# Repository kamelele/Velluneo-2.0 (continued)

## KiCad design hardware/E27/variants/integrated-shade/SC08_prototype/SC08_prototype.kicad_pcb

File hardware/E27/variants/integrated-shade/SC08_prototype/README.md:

# SC08-B experimental power-board proposal

Current status (2026-11-20): the owner accepted placement at3e261d3 and the concrete one-pair input correction published at701f616 with the actual reply “zatwierdzam”. Both decisions are recorded; hardware.json now selects the approved e229 route2 spatial input. The active native PCB is fully routed:140x100mm,47parts,957segments,54vias,6filled copper zones,8managed rule areas. Native CLI refill/save DRC reports0violations/0unconnected/0parity; the independent full matrix reports PASS382861different-net face pairs. routing-verification/ contains exact saved-CAD checks. Routing-stage independent review and human acceptance are separate from this input approval; release, Gerbers for ordering, orders and energized tests remain later gates. No physical electrical or thermal qualification has been performed.

This is the owner-authorized SC08-B native working schematic, not an orderable board. Open SC08_prototype.kicad_pro; portable local libraries are included. SC07-C remains intact at commit a6c7ed424a6aa882ef7e5b46899955d3d928f09d. The actual owner selected a laboratory prototype, ambient 0..40C, with component temperatures measured on the prototype. That scope is not new-map, schematic, placement or release approval.

## Selected corrections

Remove input L1/R1. Keep the existing film capacitors in parallel (430nF); use two TE FWFU2W220RJ series input resistors. Add STTH110A (pin1cathode to U1DRAIN, pin2anode to BUS_PLUS). Replace D3 by Vishay1.5KE440A-E3/54. Replace Q2 by PMV65XP,215 (1G2S3D). Replace C4 by CL32B226KAJNNNE22uF25VX7R1210 and add parallel C10 of the same part. Change R22 to TNPW1206210KBYEA210k and R23 to RC0805FR-074K3L4.3k for the recalculated hysteresis. Six auxiliary feed resistors change from845ohm to715ohm (CRCW2512715RFKEGHP). Their localambient condition is90C maximum; U3 effective thermal resistance must not exceed85K/W. R23limits100uAhotleakage plus5uAreserve toanOFFnode below0.5V, conditional on gateOFFstate. Other SC07 functionality, both separately fed PhotoMOS paths, base150uF160V reservoir and470ohm5W reconnect resistor remain.

The approved map contains47positions112physicalpins30nets andoneNC. Review complete physical-pin-intent.csv. New part identities and footprint geometry must be checked at capture; generic library identifiers are proposals, not a claim of completed native pad verification.

## What is actually calculated

Q2 has a manufacturer hot RDSon maximum at150C, eliminating reliance on a PNP saturation assumption. Recalculation gives5.019..6.401V gate drive, at least5.345mA to each PhotoMOS under stated rail/LED/resistor bounds,1.299mA minimum shunt current, and conditional retry below25Hz. Auxiliary-feed and local80C/85K/W U3 thermal budgets are explicit, not achieved temperatures.

Removing L1 eliminates its saturation/resonance mechanism. Peak-line connection current is bounded0.903A in the scalarRC network, total resistor energy30.28mJ. The chosen positive1kV engineering test envelope is bounded by1100V3us then60us half-value tail. With Cin>=387nF and RFpair>=396.264ohm, analytical BUS<=663.947V even with TVSopen. A700V switch still needs actual SOURCE/loop/probe margins; proposed measured VDS target is680V. The2.2kV version gives970.098V and FAILS. No general2kV or IECsurge compliance is claimed.

Whole-pulse source-energy inequality p=vs*i-R*i²<=vs²/(4R) gives COUT<=141.846V for the explicit1kV envelope, starting132V (rounded above recalculated131.086V maximum trip),120uF,shutdown.6ms and imposed1.4A residual-current bound. This does not prove a current limiter or response time. Proposed experimental fault acceptance ceiling145V replaces the earlier135V criterion only if the owner approves this packet. It stays below160V capacitor rating but requires updated pulse/discharge/fault review.

The actual own RC/samplehold21-case screen with CFB18/44/52.8uF gives averageLED43.890..58.808mA, maximumCOUT113.233V, and input-resistor pair loss up to2.681W. It is a sensitivity model, not manufacturer SPICE/PIXls or a guaranteed full-temperature envelope. Exact55mA is a calibration target; initialR2=28.7ohm, with candidate unpowered substitution menu22.1..31.6ohm to be evaluated under an engineering change. The earlier trim study is explicitly historical SC07 ideal-source evidence and is not a SC08 result.

## Prototype acceptance and physical evidence

The proposed prototype criteria in prototype-validation.json name quantities, corners and stop limits. They are plans and conditions, not completed tests. No mains, thermal, surge, optical or fault measurements occurred. Currentaccuracy, single surviving actuator attemperature, Ceff and continuous/repeated-fault resistorheat remain to be verified. In particular, the energy bound protects neither R7 against indefinite overload nor a LED module against arbitrary simultaneous faults.

Local heat is a real cost: inputresistors roughly2..2.7Wpair, auxiliaryfeed about2W, R7 about1.42W at55mA, plus IC/inductor losses. No small bulb-base size, efficiency or800lm is yet demonstrated. Placement must separate heat sources, provide solder/test access and allow qualified thermal measurements. A futureLYT5 design could reduce auxiliary loss, but requires different sensing, custom bias-wound magnetics and an actual design-tool run; it is not selected as a ready replacement.

All17 original product requirements remain controlling for the finishedlamp; original-requirements-impact.json records what this experimental scope does and does not address. Neither a prototype scope nor ERC authorizes marking physical qualification complete. No broad waivers or relaxed global rules are introduced. The standard0.2mm fabrication minimum is not a mains insulation rule. Allinput/output nets are hazardous mains-referenced; prototype testfixture/accessibility/insulation and standards assessment remain separate gates.

## Next controlled step

Actual owner approval of this exact new map and the experimental145V/test-envelope proposal is recorded in owner-capture-approval.json. Native capture is completed and checked; The owner subsequently accepted commit910870c as the experimental laboratory schematic; The owner subsequently accepted the separate LAB/spatial input and actual placement at3e261d3. Routing-stage completion and acceptance are still pending. The toolkit requires independent spatial intent before PCB placement and routing/release reviews before manufacturing files. No Gerbers, purchase or energized tests are authorized by this packet.

Primary sources: Nexperia PMV65XP product data12Feb2013; Samsung CL32B226KAJNNN official product page; ST STTH110 DS3067; Vishay88301Rev09Aug2022; TE6-2176792-5; PowerIntegrations LYT0RevB/AN60. Exact URLs are retained in the BOM and research records. Research actors and evidence limits are disclosed in workflow/schematic-08 review records.

Native capture checks are retained in workflow/integrated-shade/schematic-08/capture-checks. Requirements retain all17 original obligations; imported historical evidence is isolated under reference/SC07 and is not SC08 qualification. Native placement and partial routing now exist as stated above. No physical electrical, thermal, surge or fault test has been performed. Generic fabrication rules are not mains insulation rules.

Current PCB preparation is defined by pcb-basis/DESIGN_AUTHORITY.md and the proposed LAB fabrication crosswalk. This is a bare unpowered test-board scope proposal; original17product obligations remain in requirements.json. The actual schematic-stage prototype decision is recorded under workflow/schematic-08/pcb-planning/owner-schematic-prototype-decision.json. No PCB placement, routing or purchase acceptance follows from that decision.

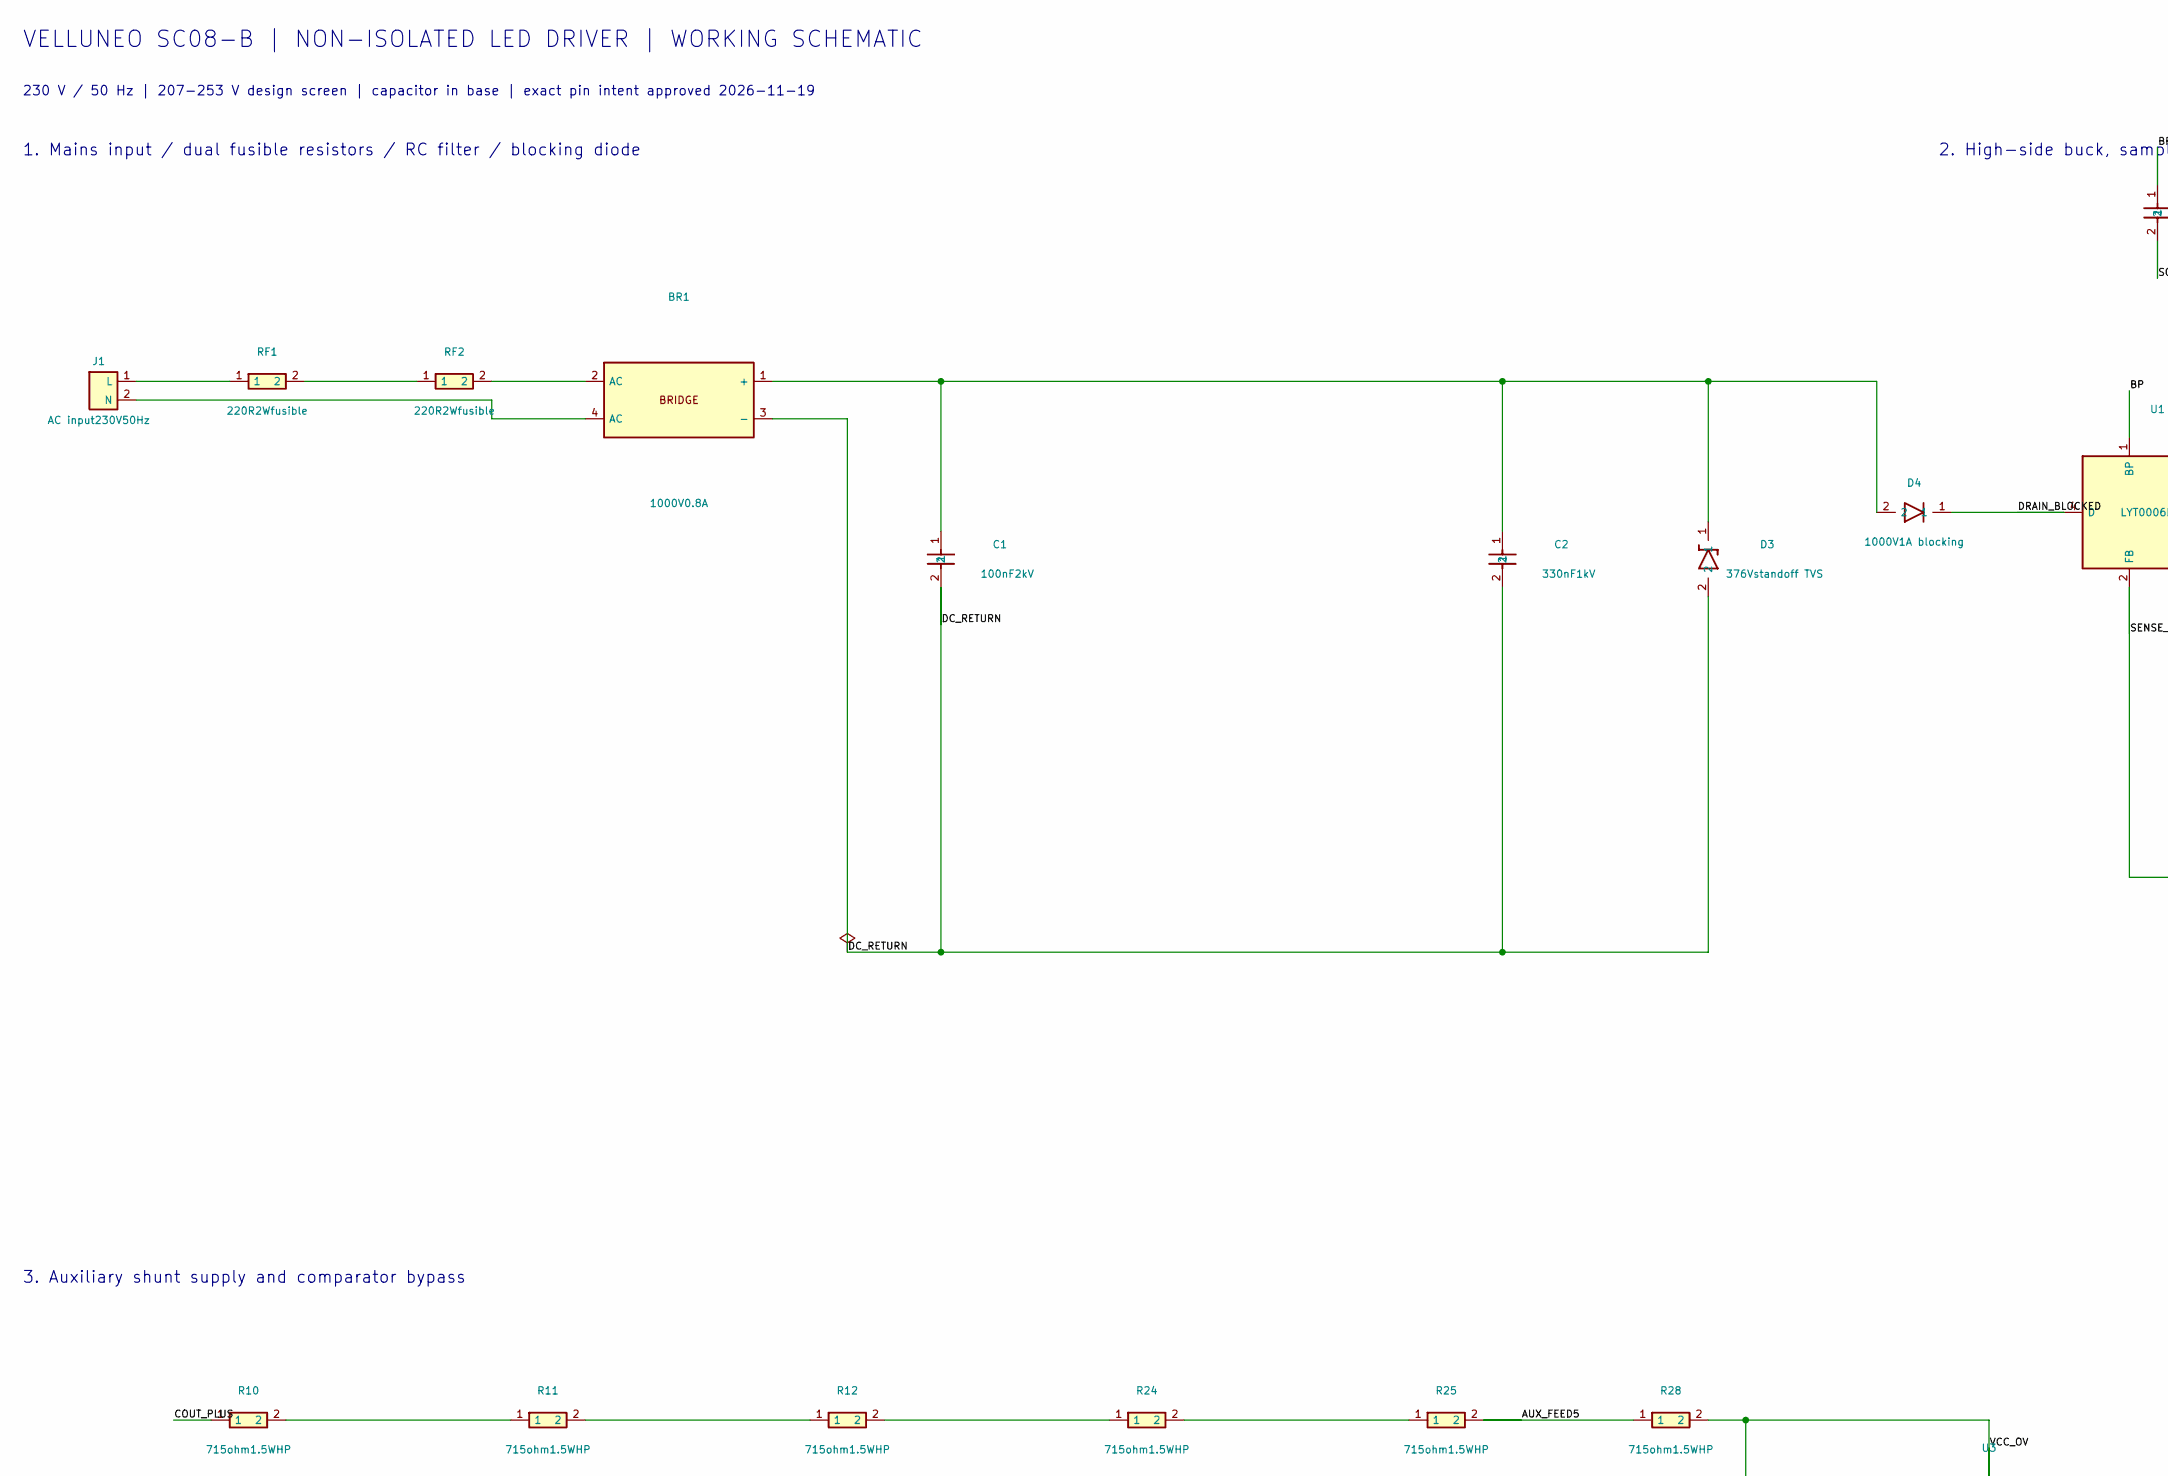
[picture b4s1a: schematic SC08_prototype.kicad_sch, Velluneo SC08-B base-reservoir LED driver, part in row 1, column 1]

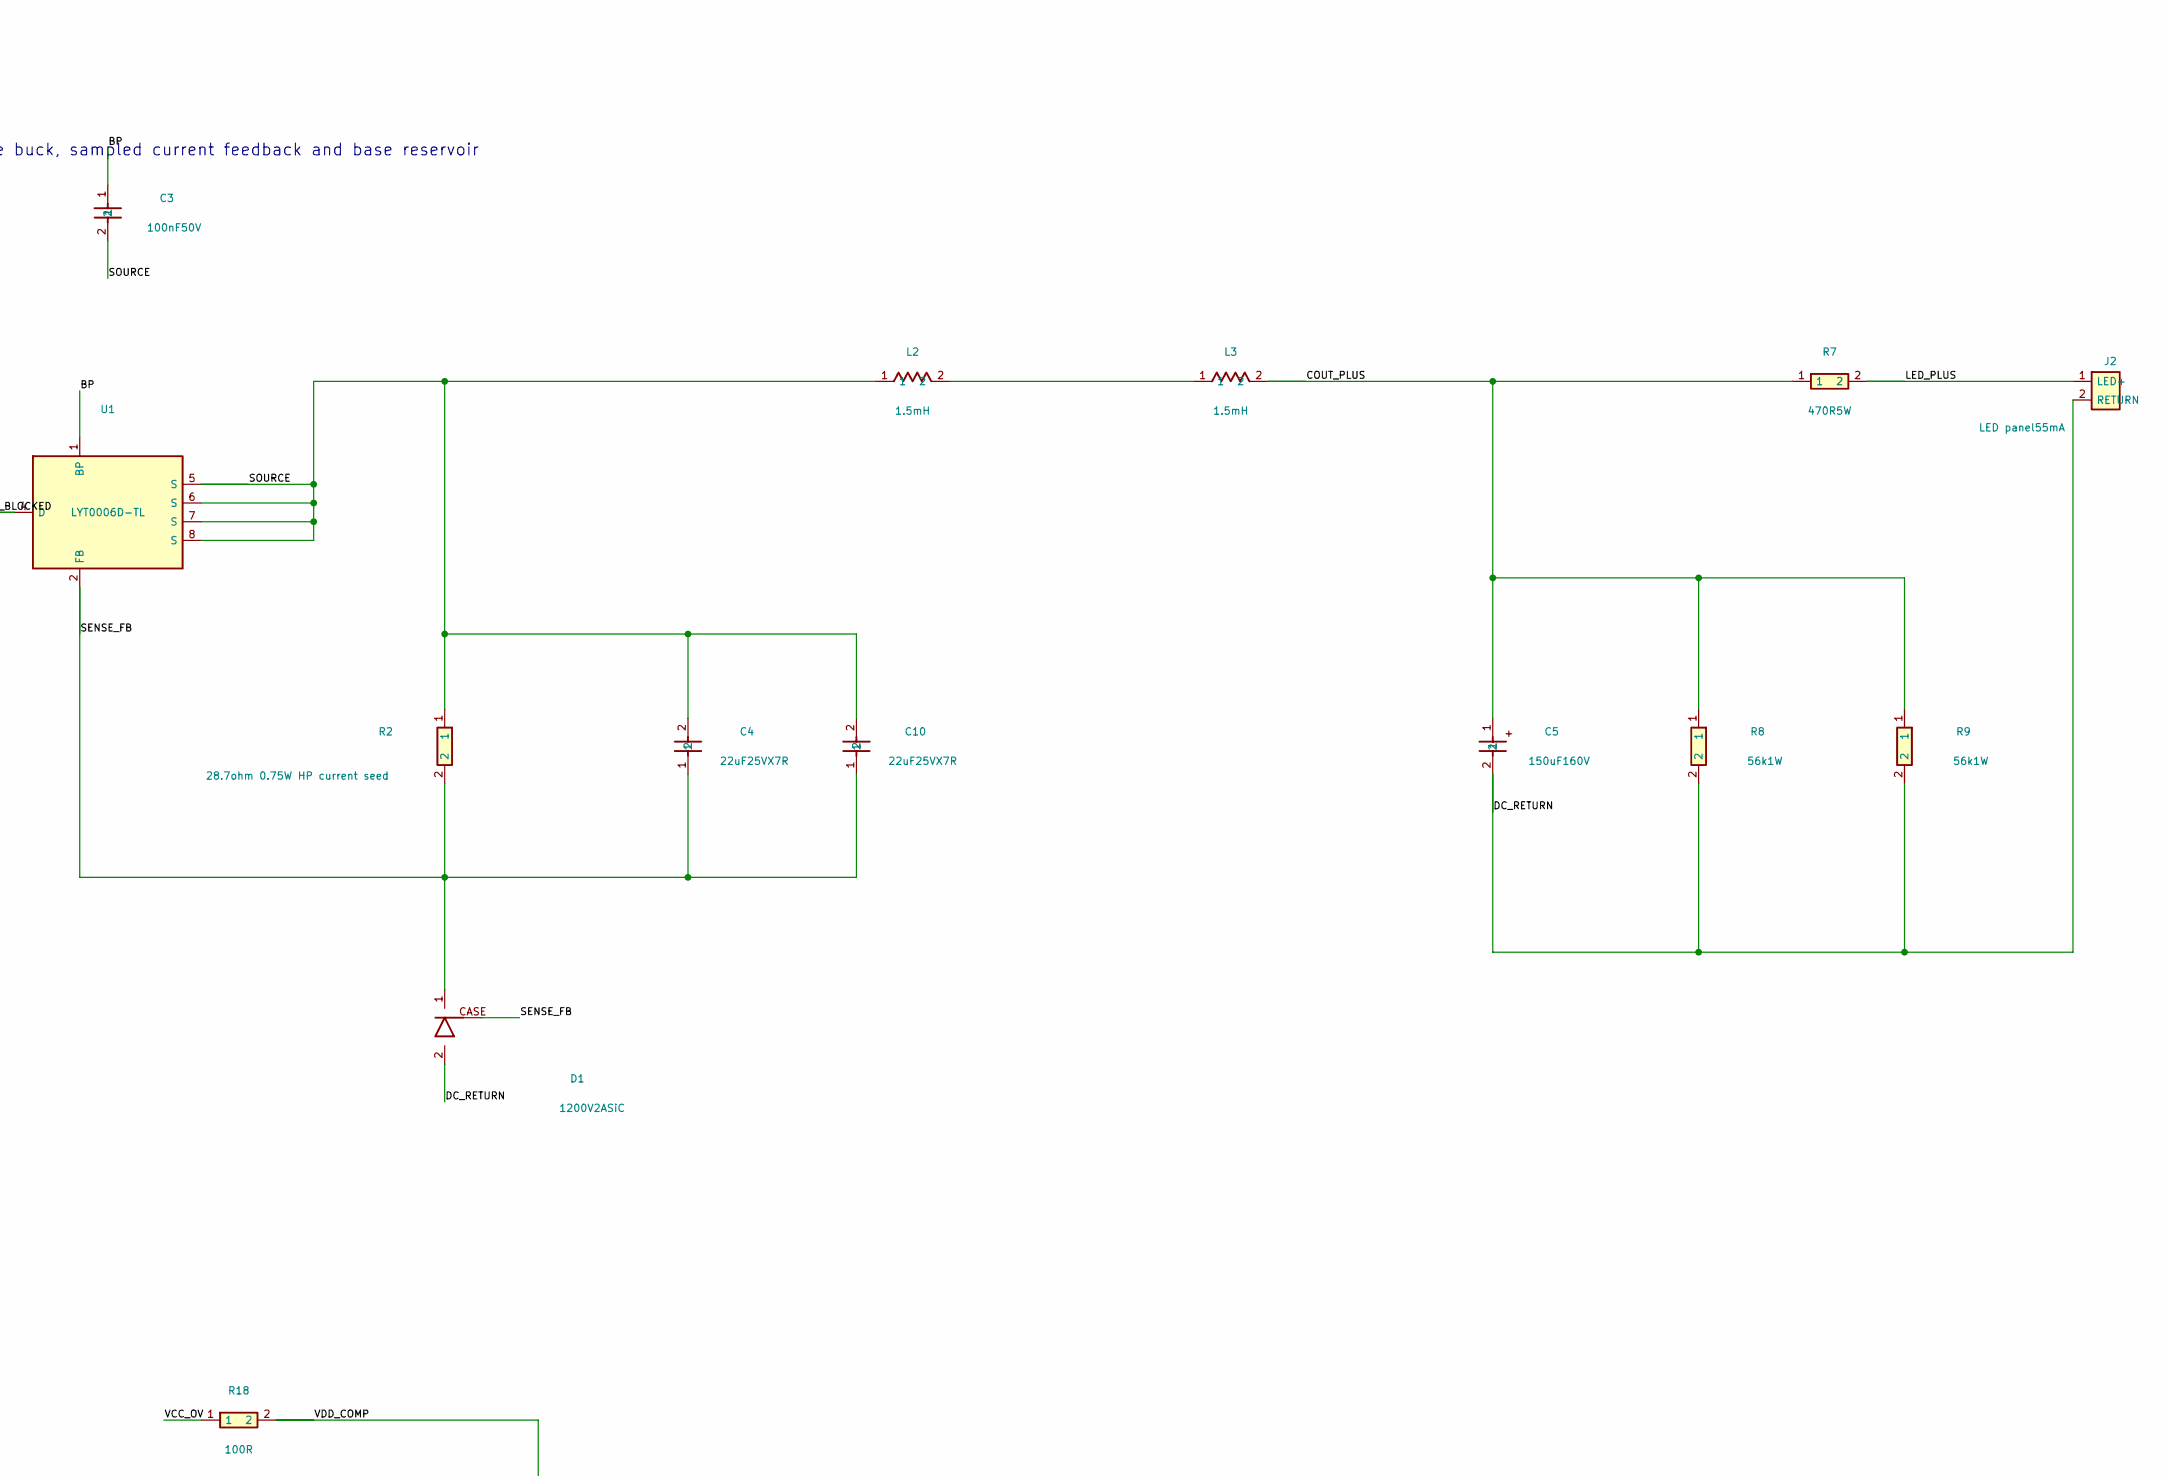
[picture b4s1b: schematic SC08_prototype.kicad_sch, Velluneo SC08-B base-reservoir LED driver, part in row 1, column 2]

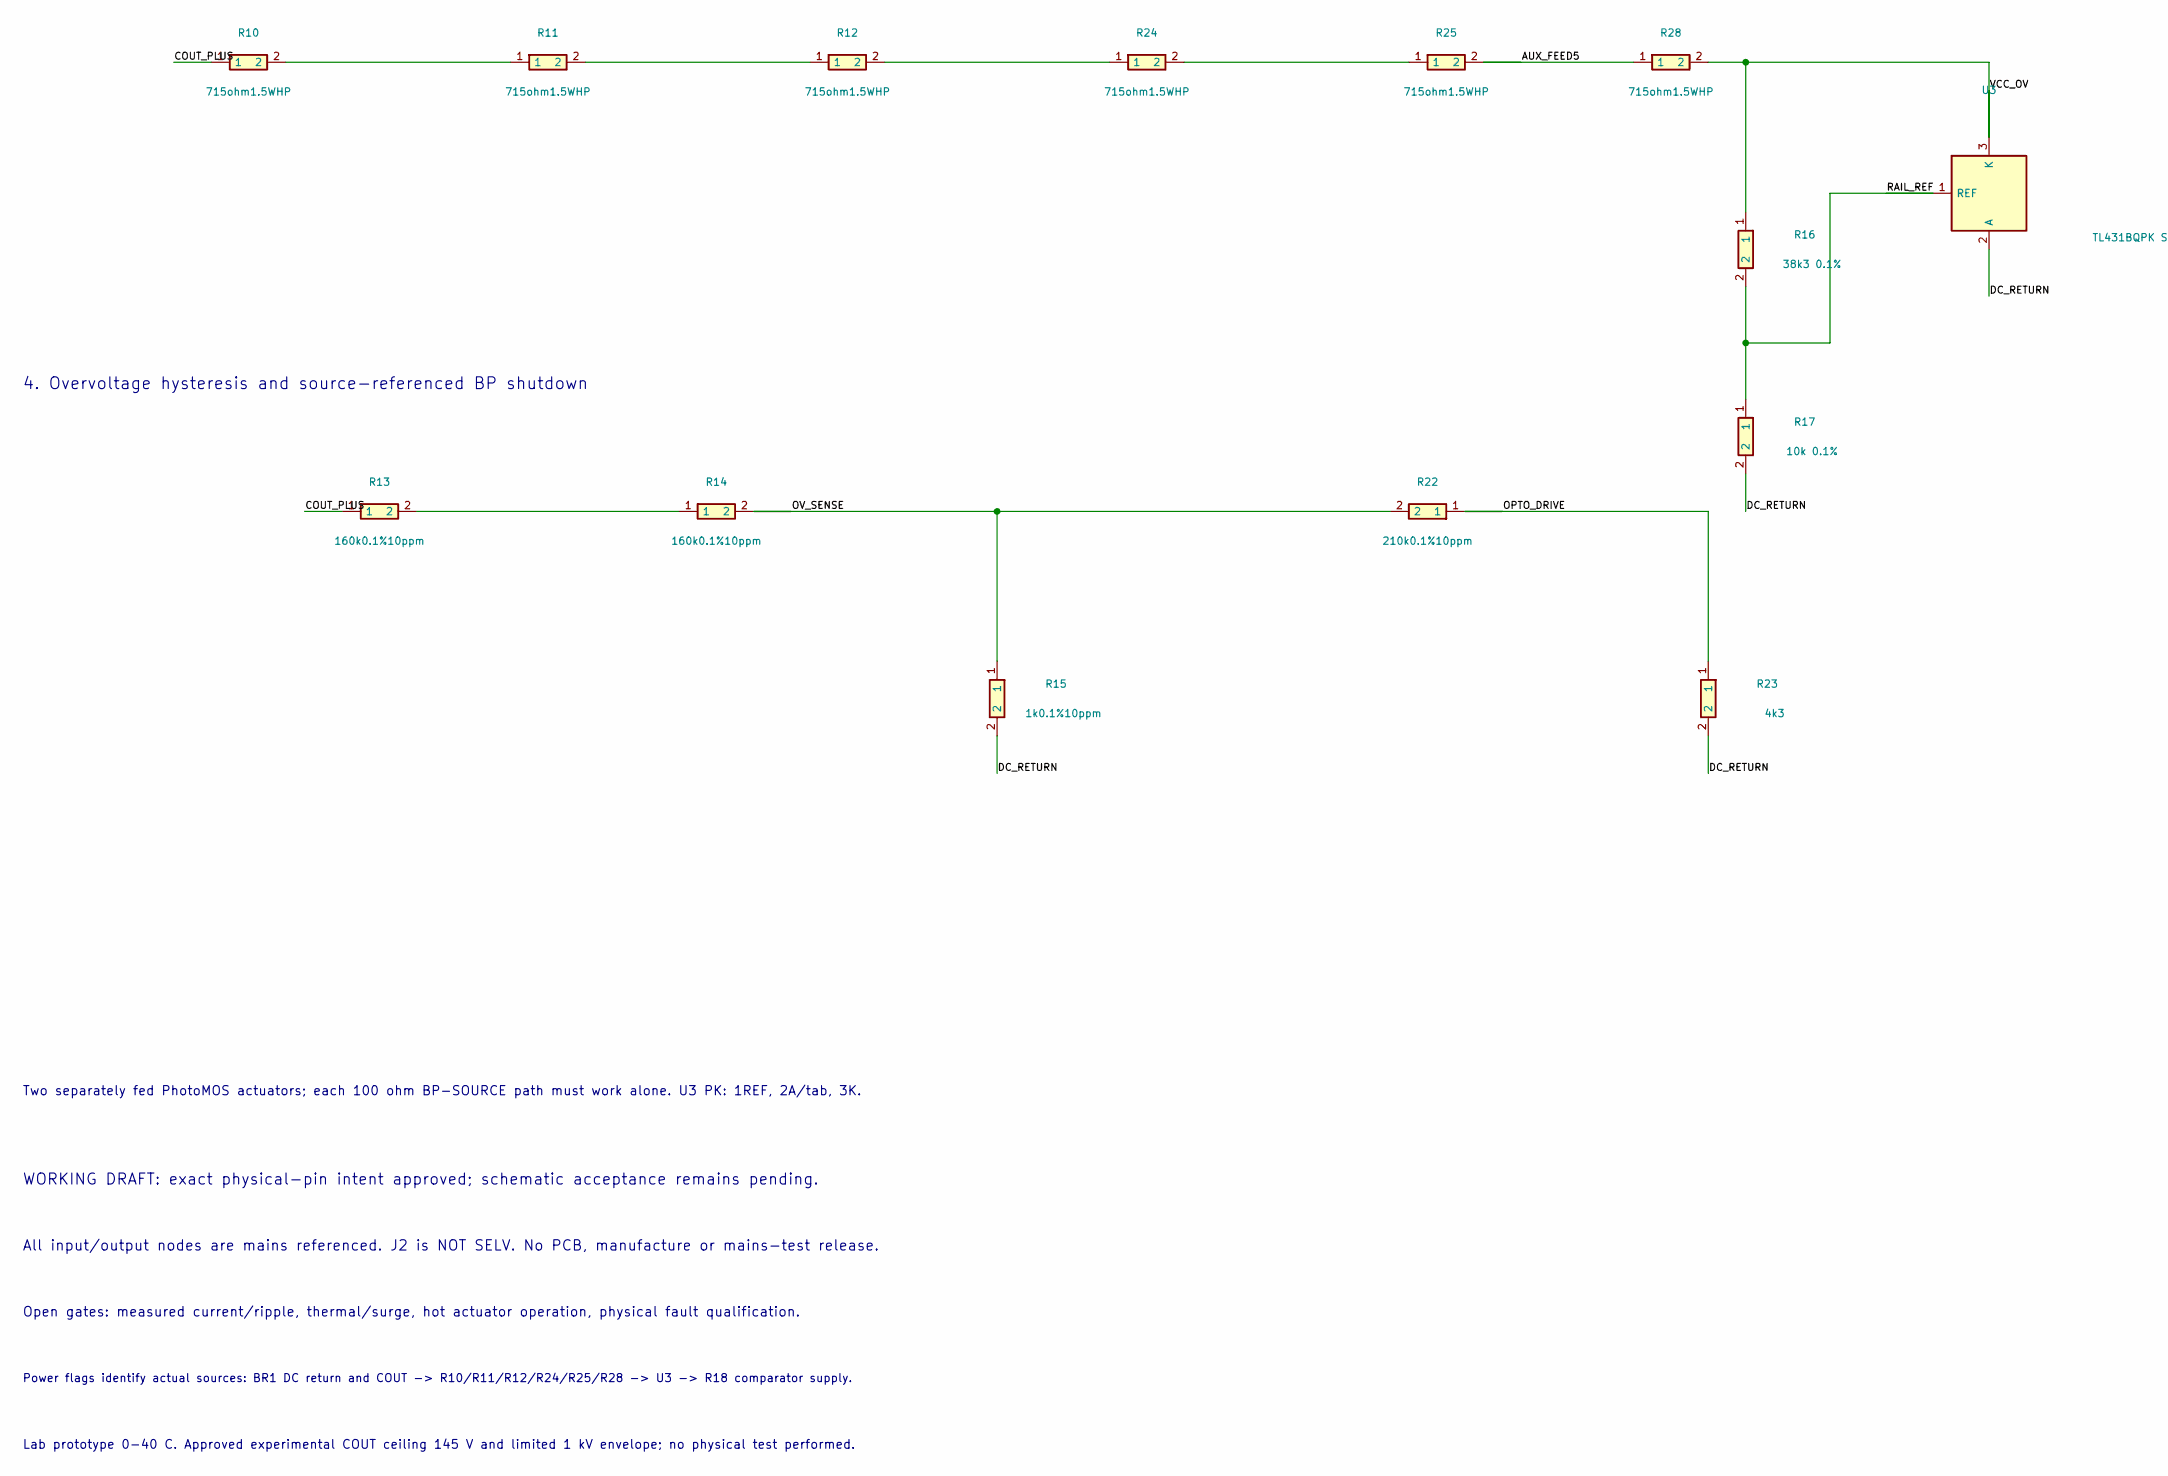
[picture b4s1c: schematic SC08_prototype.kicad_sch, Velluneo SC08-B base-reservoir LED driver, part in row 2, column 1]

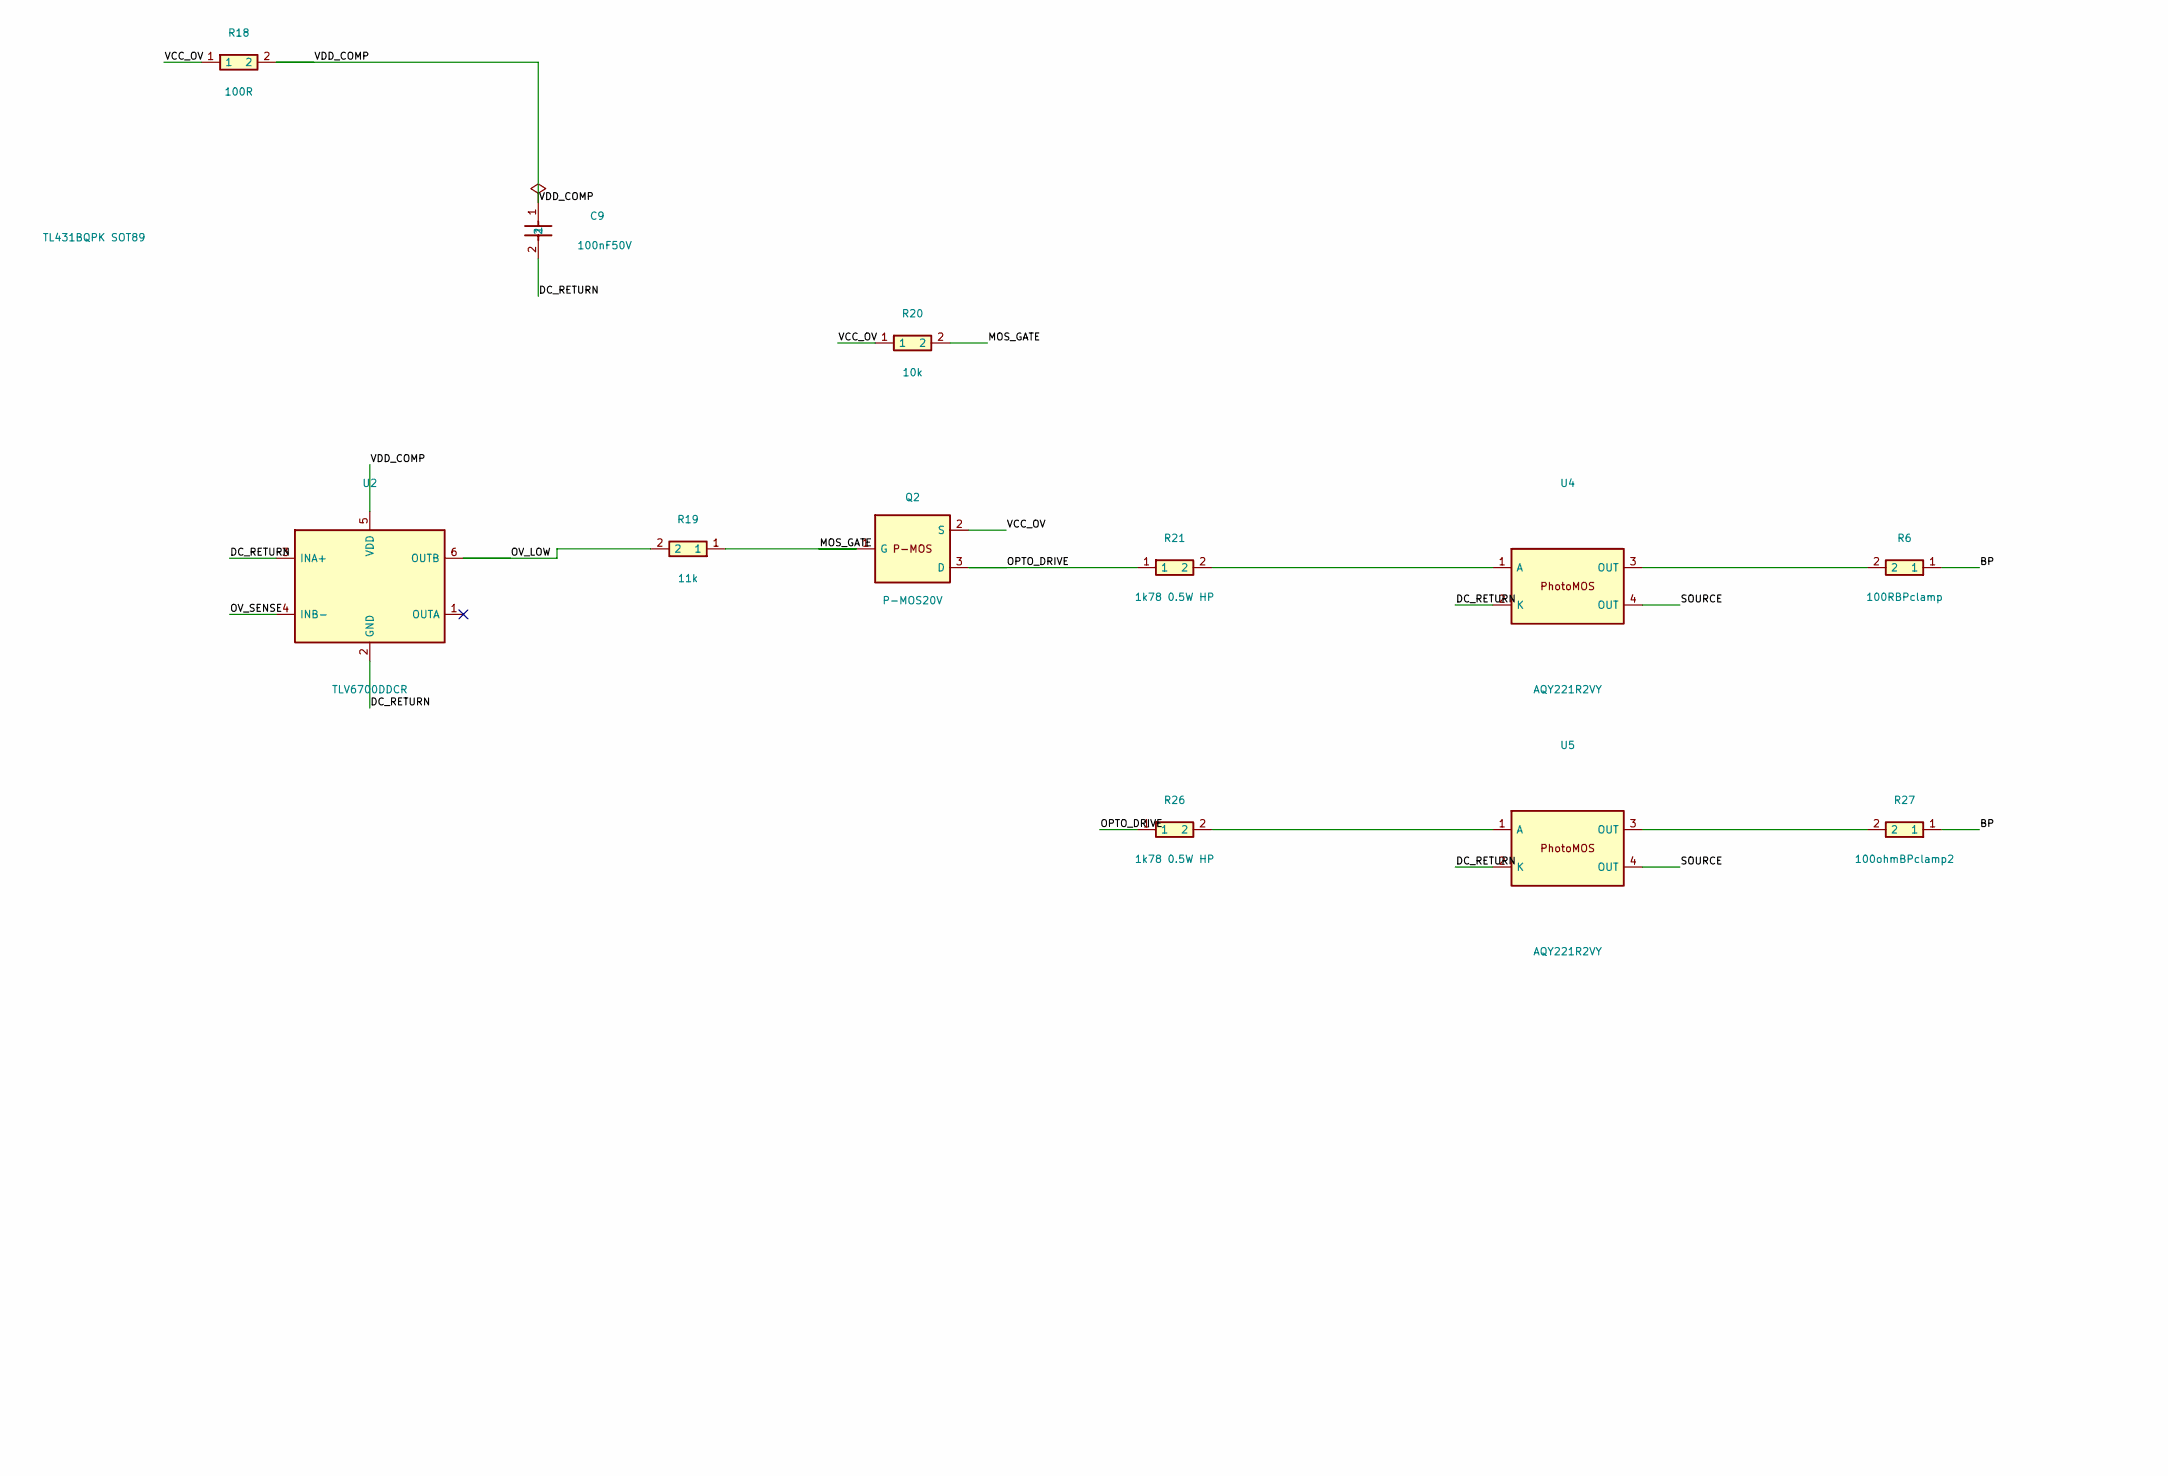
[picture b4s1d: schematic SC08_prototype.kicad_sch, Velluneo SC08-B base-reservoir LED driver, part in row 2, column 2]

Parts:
BR1: 1000V0.8A; MB10S_Diodes; MPN MB10S-13
C1: 100nF2kV; Film_32x14_P27p5; MPN R76UR31004030J
C2: 330nF1kV; Film_32x14_P27p5; MPN R76QR3330SE30J
C3, C9: 100nF50V; C_0805; MPN GRM21BR71H104KA01L
C4, C10: 22uF25VX7R; C_1210_3225Metric; MPN CL32B226KAJNNNE
C5: 150uF160V; CP_16x25_P7p5; MPN EEUED2C151
D1: 1200V2ASiC; C4D02120E_TO252; MPN C4D02120E
D3: 376Vstandoff TVS; D_DO-201AD_P15.24mm_Horizontal; MPN 1.5KE440A-E3/54
D4: 1000V1A blocking; D_SMA; MPN STTH110A
J1: AC input230V50Hz; WirePads_2_P7p5; MPN PCB wire pads, not purchased connector
J2: LED panel55mA; WirePads_2_P7p5; MPN PCB wire pads, not purchased connector
L2, L3: 1.5mH; RFC1010B_P6; MPN RFC1010B-155KE
Q2: P-MOS20V; SOT23; MPN PMV65XP,215
R2: 28.7ohm 0.75W HP current seed; R_1206; MPN CRCW120628R7FKEAHP
R6: 100RBPclamp; R_0805; MPN RC0805FR-07100RL
R7: 470R5W; AC05_18x7p5_P25p4; MPN AC05000004700JAC00
R8, R9: 56k1W; R_2512; MPN CRCW251256K0FKEG
R10, R11, R12, R24, R25, R28: 715ohm1.5WHP; R_2512; MPN CRCW2512715RFKEGHP
R13, R14: 160k0.1%10ppm; R_1206; MPN TNPW1206160KBYEA
R15: 1k0.1%10ppm; R_1206; MPN TNPW12061K00BYEA
R16: 38k3 0.1%; R_1206; MPN TNPW120638K3BEEA
R17: 10k 0.1%; R_1206; MPN TNPW120610K0BEEA
R18: 100R; R_0805; MPN RC0805FR-07100RL
R19: 11k; R_0805; MPN RC0805FR-0711KL
R20: 10k; R_0805; MPN RC0805FR-0710KL
R21, R26: 1k78 0.5W HP; R_0805; MPN CRCW08051K78FKEAHP
R22: 210k0.1%10ppm; R_1206; MPN TNPW1206210KBYEA
R23: 4k3; R_0805; MPN RC0805FR-074K3L
R27: 100ohmBPclamp2; R_0805; MPN RC0805FR-07100RL
RF1, RF2: 220R2Wfusible; RF_16x5p5_P22; MPN FWFU2W220RJ
U1: LYT0006D-TL; LYT_SO8C_no3; MPN LYT0006D-TL
U2: TLV6700DDCR; SOT23_6; MPN TLV6700DDCR
U3: TL431BQPK SOT89; SOT-89-3; MPN TL431BQPK
U4, U5: AQY221R2VY; Panasonic_SSOP4; MPN AQY221R2VY

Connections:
/AUX_FEED5: R25.2, R28.1
/BP: C3.1, R6.1, R27.1, U1.1 (BP)
/COUT_PLUS: C5.1, L3.2, R7.1, R8.1, R9.1, R10.1, R13.1
/DC_RETURN: BR1.3 (-), C1.2, C2.2, C5.2, C9.2, D1.2 (A), D3.2, J2.2 (RETURN), R8.2, R9.2, R15.2, R17.2, R23.2, U2.2 (GND), U2.3 (INA+), U3.2 (A), U4.2 (K), U5.2 (K)
/DRAIN_BLOCKED: D4.1, U1.4 (D)
/LED_PLUS: J2.1 (LED+), R7.2
/MOS_GATE: Q2.1 (G), R19.1, R20.2
/OPTO_DRIVE: Q2.3 (D), R21.1, R22.1, R23.1, R26.1
/OV_LOW: R19.2, U2.6 (OUTB)
/OV_SENSE: R14.2, R15.1, R22.2, U2.4 (INB-)
/RAIL_REF: R16.2, R17.1, U3.1 (REF)
/SENSE_FB: C4.1, C10.1, D1.1 (K), D1.CASE (CASE(K)), R2.2, U1.2 (FB)
/SOURCE: C3.2, C4.2, C10.2, L2.1, R2.1, U1.5 (S), U1.6 (S), U1.7 (S), U1.8 (S), U4.4 (OUT), U5.4 (OUT)
/VCC_OV: Q2.2 (S), R16.1, R18.1, R20.1, R28.2, U3.3 (K)
/VDD_COMP: C9.1, R18.2, U2.5 (VDD)
unnamed: BR1.1 (+), C1.1, C2.1, D3.1, D4.2
unnamed: BR1.2 (AC), RF2.2
unnamed: J1.1 (L), RF1.1
unnamed: BR1.4 (AC), J1.2 (N)
unnamed: L2.2, L3.1
unnamed: R6.2, U4.3 (OUT)
unnamed: R10.2, R11.1
unnamed: R11.2, R12.1
unnamed: R12.2, R24.1
unnamed: R13.2, R14.1
unnamed: R24.2, R25.1
unnamed: R27.2, U5.3 (OUT)
unnamed: RF1.2, RF2.1
unnamed: R21.2, U4.1 (A)
unnamed: R26.2, U5.1 (A)

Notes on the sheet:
VELLUNEO SC08-B | NON-ISOLATED LED DRIVER | WORKING SCHEMATIC
230 V / 50 Hz | 207-253 V design screen | capacitor in base | exact pin intent approved 2026-11-19
1. Mains input / dual fusible resistors / RC filter / blocking diode
2. High-side buck, sampled current feedback and base reservoir
3. Auxiliary shunt supply and comparator bypass
4. Overvoltage hysteresis and source-referenced BP shutdown
Two separately fed PhotoMOS actuators; each 100 ohm BP-SOURCE path must work alone. U3 PK: 1REF, 2A/tab, 3K.
WORKING DRAFT: exact physical-pin intent approved; schematic acceptance remains pending.
All input/output nodes are mains referenced. J2 is NOT SELV. No PCB, manufacture or mains-test release.
Open gates: measured current/ripple, thermal/surge, hot actuator operation, physical fault qualification.
Power flags identify actual sources: BR1 DC return and COUT -> R10/R11/R12/R24/R25/R28 -> U3 -> R18 comparator supply.
Lab prototype 0-40 C. Approved experimental COUT ceiling 145 V and limited 1 kV envelope; no physical test performed.

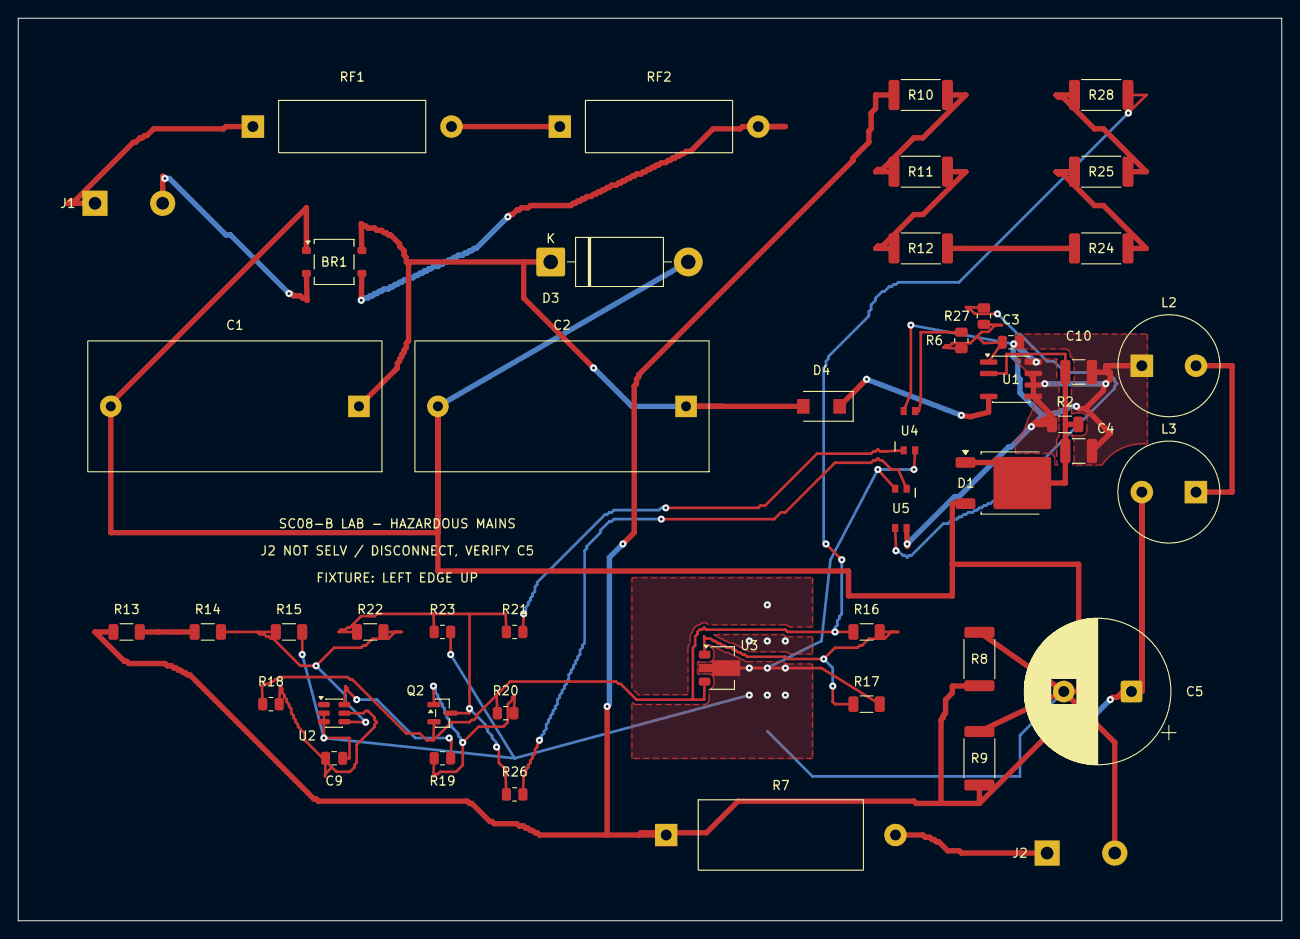
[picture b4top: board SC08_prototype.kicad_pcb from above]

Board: 2 copper layers, 140.0 x 100.0 mm, 47 parts (0 on the bottom side), 30 nets.
